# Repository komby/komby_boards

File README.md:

ftdi_prog
=========

Eagle files for the komby FTDI programmers

for more information visit http://www.komby.com/ftdi_prog

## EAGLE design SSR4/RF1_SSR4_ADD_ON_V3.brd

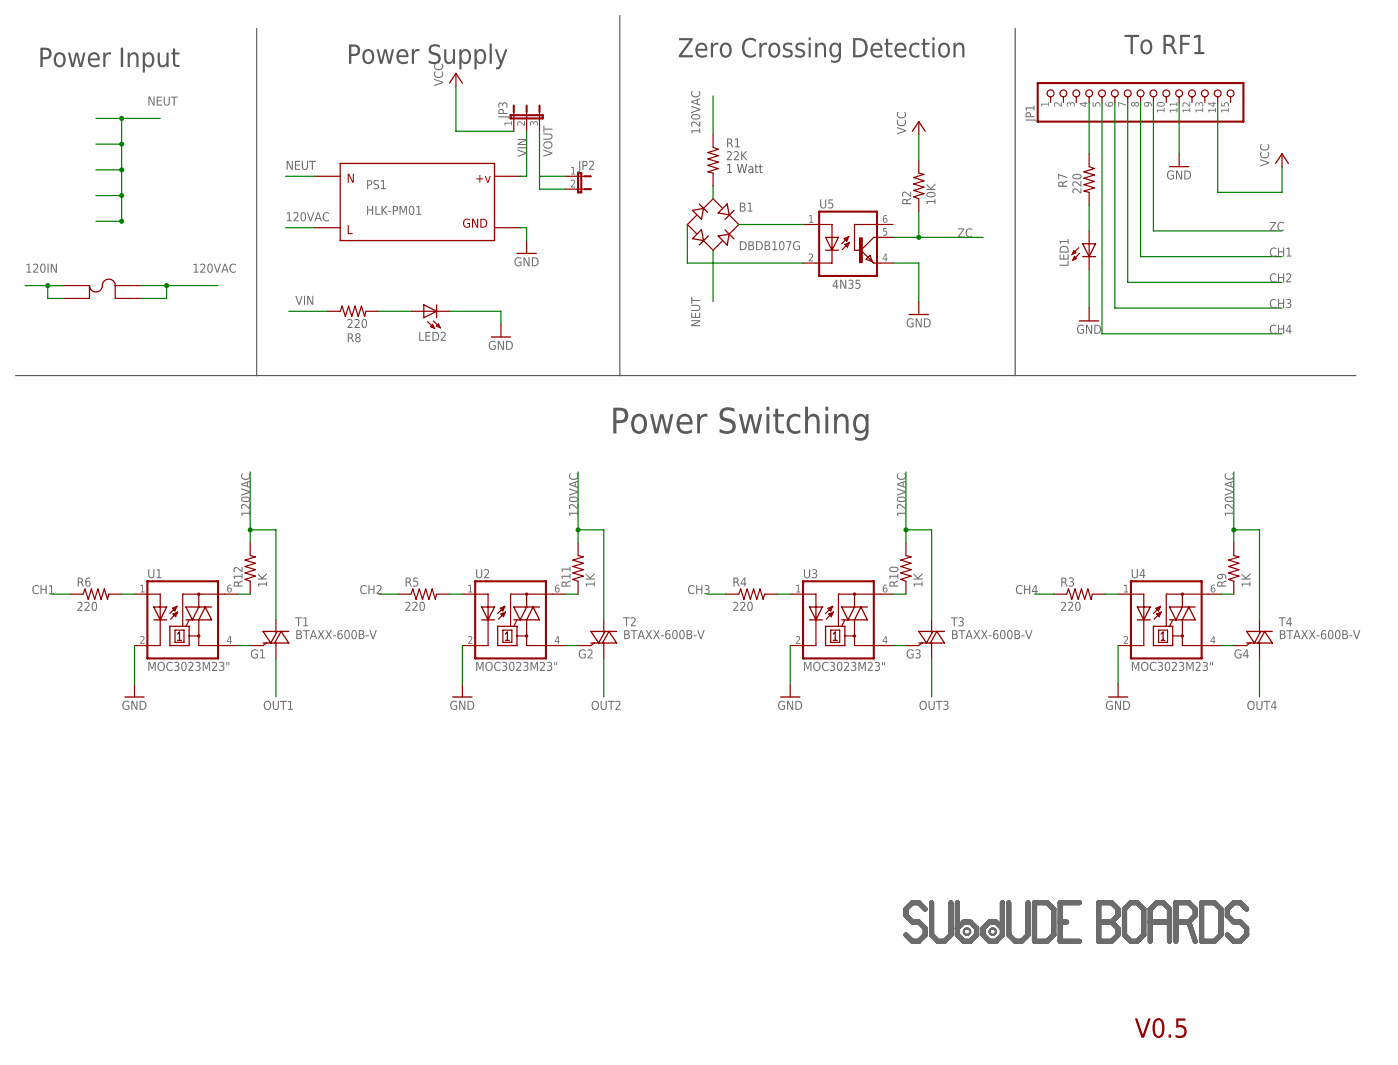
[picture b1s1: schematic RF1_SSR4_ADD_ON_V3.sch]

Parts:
B1: DBDB107G; DB
F1: FUSE5MMPCB; KE3517
JP1: PINHD-1X15; 1X15
JP2: JP1E; JP1
JP3: JP2E; JP2
LED1, LED2: LED3MM
PS1: HLK-PM01; HLK-PM01-STD
R1: 22K; 0617V
R2: 10K; 0207/7
R3, R4, R5, R6, R7, R8: 220; 0207/2V
R9, R10, R11, R12: 1K; 0207/2V
T1, T2, T3, T4: BTAXX-600B-V; TO220BV
U1, U2, U3, U4: MOC3023M23"; DIL06A
U5: 4N35SMALL; DIL06A
U$1, U$2: SUBDUDE_LOGOLARGE; SUBDUDE_LARGE

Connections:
120IN: F1.P$1, F1.P$3
120VAC: F1.P$2, F1.P$4, PS1.AC_L, R1.1, R9.2, R10.2, R11.2, R12.2, T1.T2 (A2), T2.T2 (A2), T3.T2 (A2), T4.T2 (A2)
CH1: JP1.8, R6.1
CH2: JP1.7, R5.1
CH3: JP1.6, R4.1
CH4: JP1.5, R3.1
G1: T1.G, U1.4 (A1)
G2: T2.G, U2.4 (A1)
G3: T3.G, U3.4 (A1)
G4: T4.G, U4.4 (A1)
GND: JP1.11, LED1.K (C), LED2.K (C), PS1.VO-, U1.2 (C), U2.2 (C), U3.2 (C), U4.2 (C), U5.4 (EMI)
unnamed: LED1.A, R7.2
unnamed: B1.AC1, R1.2
unnamed: JP1.4, R7.1
unnamed: LED2.A, R8.2
unnamed: B1.+, U5.1 (A)
unnamed: B1.-, U5.2 (C)
unnamed: R4.2, U3.1 (A)
unnamed: R5.2, U2.1 (A)
unnamed: R6.2, U1.1 (A)
unnamed: R9.1, U4.6 (A2)
unnamed: R10.1, U3.6 (A2)
unnamed: R11.1, U2.6 (A2)
unnamed: R12.1, U1.6 (A2)
NEUT: B1.AC2, PS1.AC_N
OUT1: T1.T1 (A1)
OUT2: T2.T1 (A1)
OUT3: T3.T1 (A1)
OUT4: T4.T1 (A1)
QQQQ: R3.2, U4.1 (A)
VCC: JP1.14, JP3.1, R2.2
VIN: JP3.2, PS1.VO+, R8.1
VOUT: JP2.1, JP2.2, JP3.3
ZC: JP1.9, R2.1, U5.5 (COL)

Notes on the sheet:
V0.5
Zero Crossing Detection
1 Watt
4N35
Power Supply
Power Input
To RF1
Power Switching

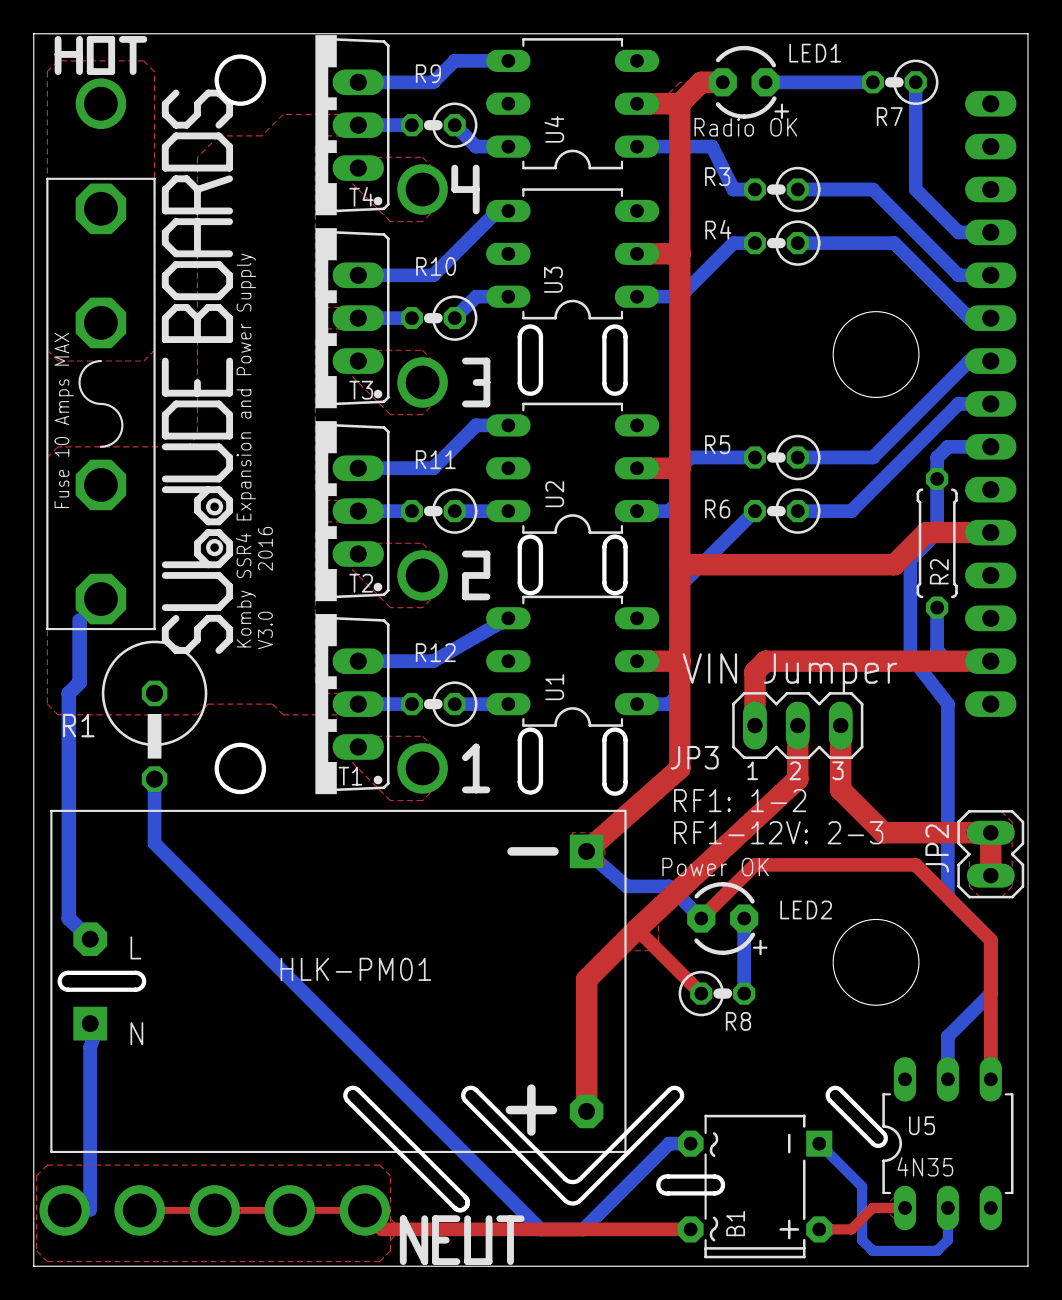
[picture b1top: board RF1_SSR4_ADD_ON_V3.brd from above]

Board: 2 copper layers, 58.9 x 73.0 mm, 31 parts (1 on the bottom side), 30 nets.

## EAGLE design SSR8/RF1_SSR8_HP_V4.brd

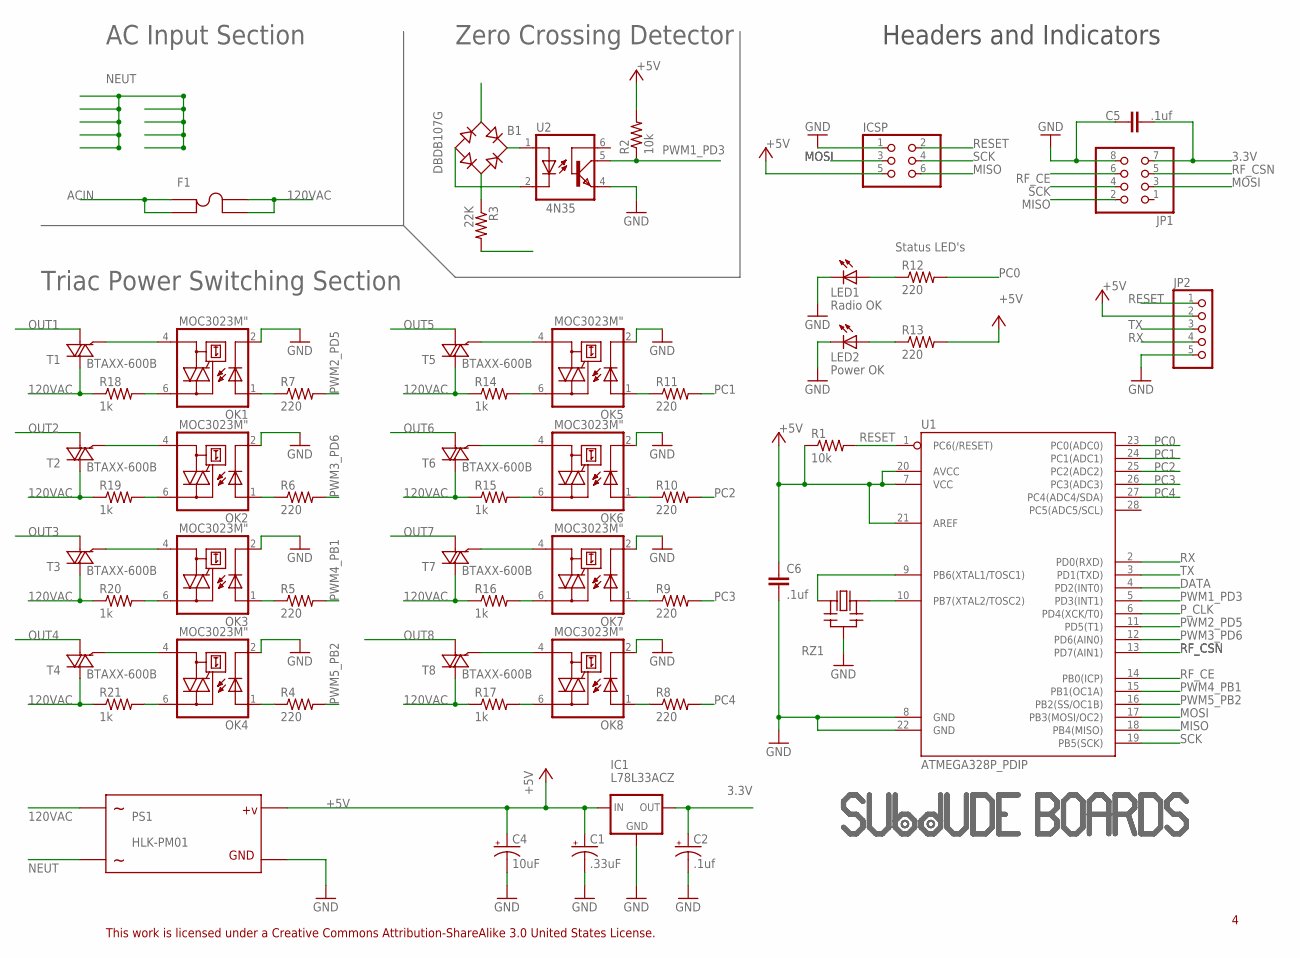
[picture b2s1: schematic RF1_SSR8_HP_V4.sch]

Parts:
B1: DBDB107G; DB
C1: .33uF; E1,8-4
C2: .1uf; E1,8-4
C4: 10uF; E1,8-4
C5, C6: .1uf; C025-024X044
F1: FUSE5MMPCB; KE3517
IC1: L78L33ACZ; 78LXX
ICSP: PINHD-2X3; 2X03
JP1: PINHD-2X4; 2X04
JP2: PINHD-1X51X05-BIG; 1X05-BIG
LED1, LED2: LED3MM
OK1, OK2, OK3, OK4, OK5, OK6, OK7, OK8: MOC3023M"; DIL06A
PS1: HLK-PM01; HLK-PM01-STD
R1: 10k; 0207/7
R2: 10k; 0207/2V
R3: 22K; 0411/12
R4, R5, R6, R7, R8, R9, R10, R11, R12, R13: 220; 0207/2V
R14, R15, R16, R17, R18, R19, R20, R21: 1k; 0207/2V
RZ1: CERMOSCILL-THM; CERM_OSC
T1, T2, T3, T4, T5, T6, T7, T8: BTAXX-600B; TO220BVA
U1: ATMEGA328P_PDIP; DIL28-3
U2: 4N35SMALL; DIL06A
U$2: SUBDUDE_LOGOLARGE; SUBDUDE_LARGE
U$3: SUBDUDE_LOGOSMALL; SUBDUDE_SMALL

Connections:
3.3V: C2.+, C5.2, IC1.OUT, JP1.7
120VAC: F1.P$2, F1.P$4, PS1.AC_N, R3.2, R14.1, R15.1, R16.1, R17.1, R18.1, R19.1, R20.1, R21.1, T1.T2 (A2), T2.T2 (A2), T3.T2 (A2), T4.T2 (A2), T5.T2 (A2), T6.T2 (A2), T7.T2 (A2), T8.T2 (A2)
+5V: C1.+, C4.+, C6.1, IC1.IN, ICSP.5, JP2.2, PS1.VO+, R1.1, R2.2, R13.2, U1.7 (VCC), U1.20 (AVCC), U1.21 (AREF)
ACIN: F1.P$1, F1.P$3
DATA: U1.4 (PD2(INT0))
GND: C1.-, C2.-, C4.-, C5.1, C6.2, IC1.GND, ICSP.1, JP1.8, JP2.5, LED1.K (C), LED2.K (C), OK1.2 (C), OK2.2 (C), OK3.2 (C), OK4.2 (C), OK5.2 (C), OK6.2 (C), OK7.2 (C), OK8.2 (C), PS1.VO-, RZ1.P$2 (GND), U1.8 (GND), U1.22 (GND), U2.4 (EMI)
MISO: ICSP.6, JP1.2, U1.18 (PB4(MISO))
MOSI: ICSP.3, JP1.3, U1.17 (PB3(MOSI/OC2))
unnamed: OK1.1 (A), R7.1
unnamed: OK2.1 (A), R6.1
unnamed: OK3.1 (A), R5.1
unnamed: OK4.1 (A), R4.1
unnamed: RZ1.P$3 (OUT), U1.10 (PB7(XTAL2/TOSC2))
unnamed: RZ1.P$1 (IN), U1.9 (PB6(XTAL1/TOSC1))
unnamed: OK5.1 (A), R11.1
unnamed: OK6.1 (A), R10.1
unnamed: OK7.1 (A), R9.1
unnamed: OK8.1 (A), R8.1
unnamed: B1.AC2, R3.1
unnamed: OK1.6 (A2), R18.2
unnamed: OK1.4 (A1), T1.G
unnamed: OK2.6 (A2), R19.2
unnamed: OK2.4 (A1), T2.G
unnamed: OK3.6 (A2), R20.2
unnamed: OK3.4 (A1), T3.G
unnamed: OK4.6 (A2), R21.2
unnamed: B1.-, U2.2 (C)
unnamed: B1.+, U2.1 (A)
unnamed: OK4.4 (A1), T4.G
unnamed: LED1.A, R12.1
unnamed: LED2.A, R13.1
unnamed: OK5.4 (A1), T5.G
unnamed: OK5.6 (A2), R14.2
unnamed: OK6.4 (A1), T6.G
unnamed: OK6.6 (A2), R15.2
unnamed: OK7.4 (A1), T7.G
unnamed: OK7.6 (A2), R16.2
unnamed: OK8.6 (A2), R17.2
unnamed: OK8.4 (A1), T8.G
NEUT: B1.AC1, PS1.AC_L
OUT1: T1.T1 (A1)
OUT2: T2.T1 (A1)
OUT3: T3.T1 (A1)
OUT4: T4.T1 (A1)
OUT5: T5.T1 (A1)
OUT6: T6.T1 (A1)
OUT7: T7.T1 (A1)
OUT8: T8.T1 (A1)
PC0: R12.2, U1.23 (PC0(ADC0))
PC1: R11.2, U1.24 (PC1(ADC1))
PC2: R10.2, U1.25 (PC2(ADC2))
PC3: R9.2, U1.26 (PC3(ADC3))
PC4: R8.2, U1.27 (PC4(ADC4/SDA))
PWM1_PD3: R2.1, U1.5 (PD3(INT1)), U2.5 (COL)
PWM2_PD5: R7.2, U1.11 (PD5(T1))
PWM3_PD6: R6.2, U1.12 (PD6(AIN0))
PWM4_PB1: R5.2, U1.15 (PB1(OC1A))
PWM5_PB2: R4.2, U1.16 (PB2(SS/OC1B))
P_CLK: U1.6 (PD4(XCK/T0))
RESET: ICSP.2, JP2.1, R1.2, U1.1 (PC6(/RESET))
RF_CE: JP1.6, U1.14 (PB0(ICP))
RF_CSN: JP1.5, U1.13 (PD7(AIN1))
RX: JP2.4, U1.2 (PD0(RXD))
SCK: ICSP.4, JP1.4, U1.19 (PB5(SCK))
TX: JP2.3, U1.3 (PD1(TXD))

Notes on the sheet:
This work is licensed under a Creative Commons Attribution-ShareAlike 3.0 United States License.
AC Input Section
Status LED's
Zero Crossing Detector
Triac Power Switching Section
Power OK
Radio OK
Headers and Indicators
4N35

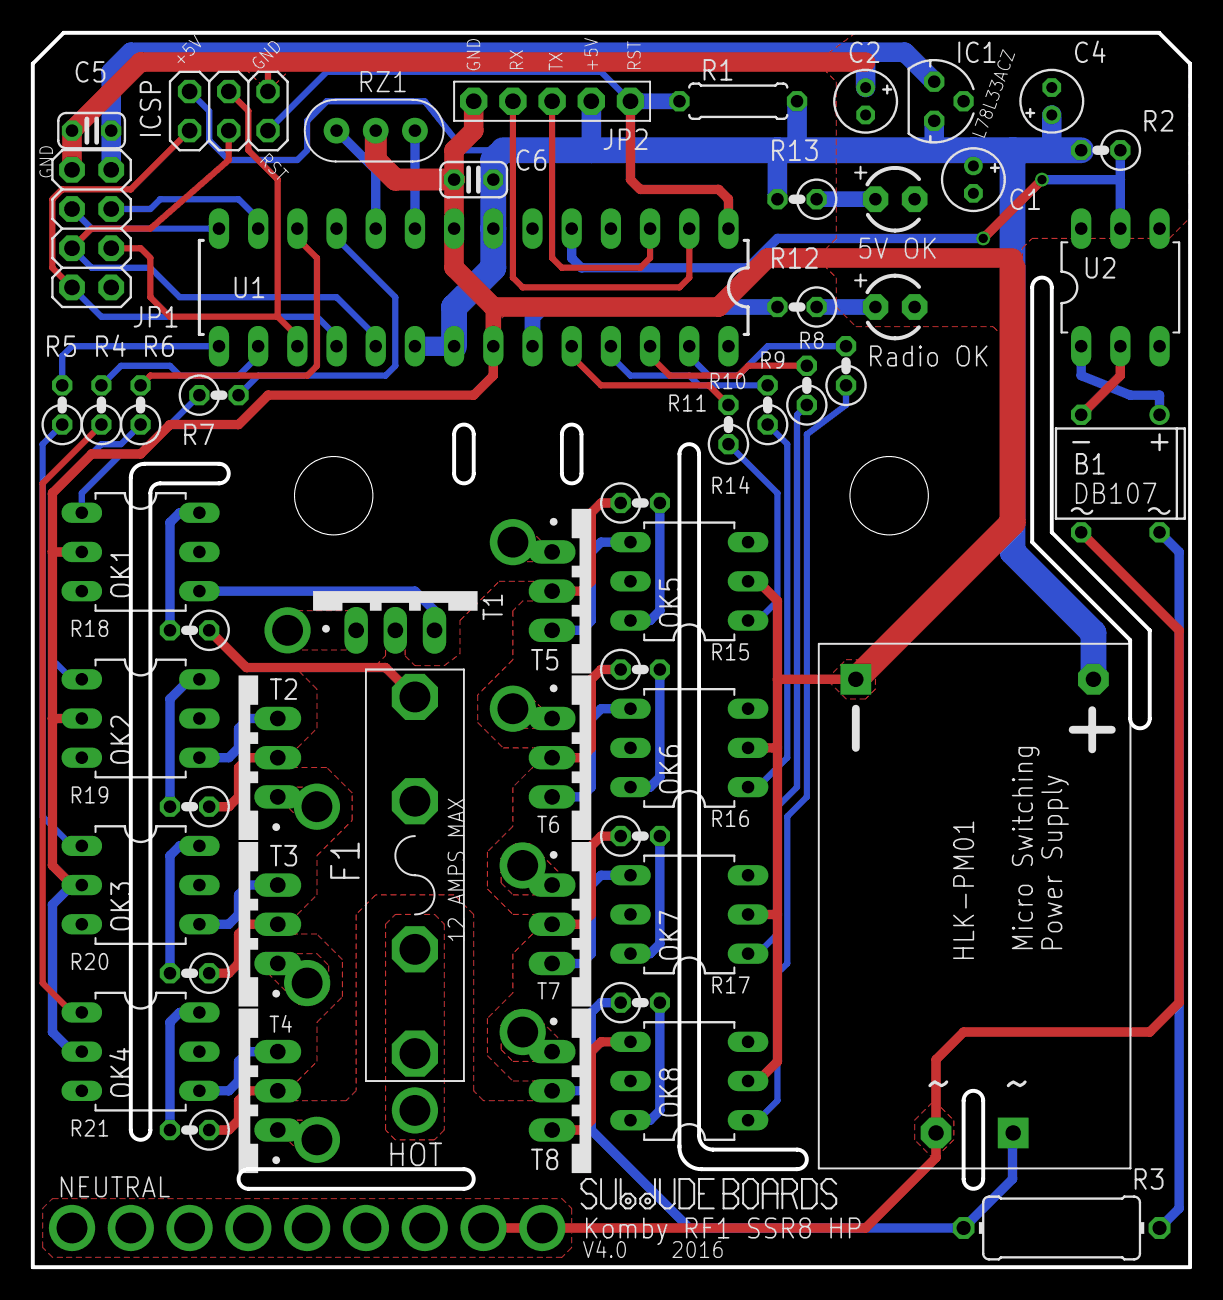
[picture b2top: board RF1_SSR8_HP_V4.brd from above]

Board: 2 copper layers, 75.0 x 80.0 mm, 56 parts (1 on the bottom side), 55 nets.

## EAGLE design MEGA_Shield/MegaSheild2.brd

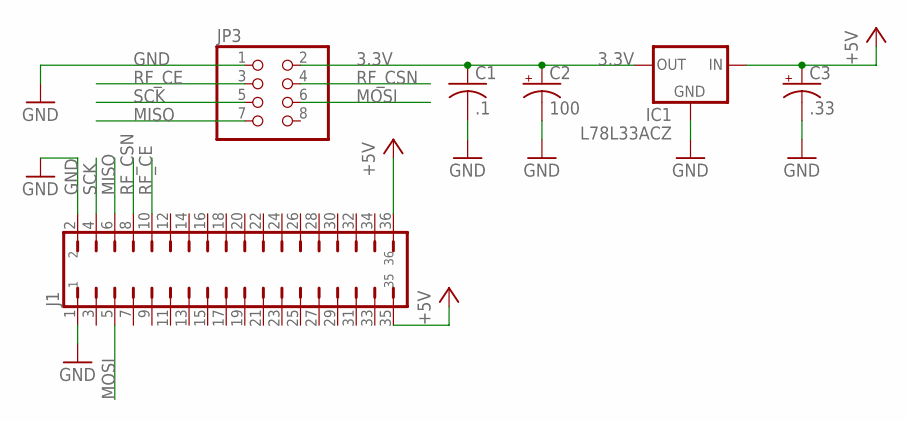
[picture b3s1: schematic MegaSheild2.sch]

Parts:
C1: .1; C025-024X044
C2: 100; E2,5-6
C3: .33; E1,8-4
IC1: L78L33ACZ; 78LXX
J1: JP18Q2X18BIG; 2X18-BIG
JP3: PINHD-2X4; 2X04

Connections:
3.3V: C1.1, C2.+, IC1.OUT, JP3.2
+5V: C3.+, IC1.IN, J1.35, J1.36
GND: C1.2, C2.-, C3.-, IC1.GND, J1.1, J1.2, JP3.1
MISO: J1.6, JP3.7
MOSI: J1.5, JP3.6
RF_CE: J1.10, JP3.3
RF_CSN: J1.8, JP3.4
SCK: J1.4, JP3.5

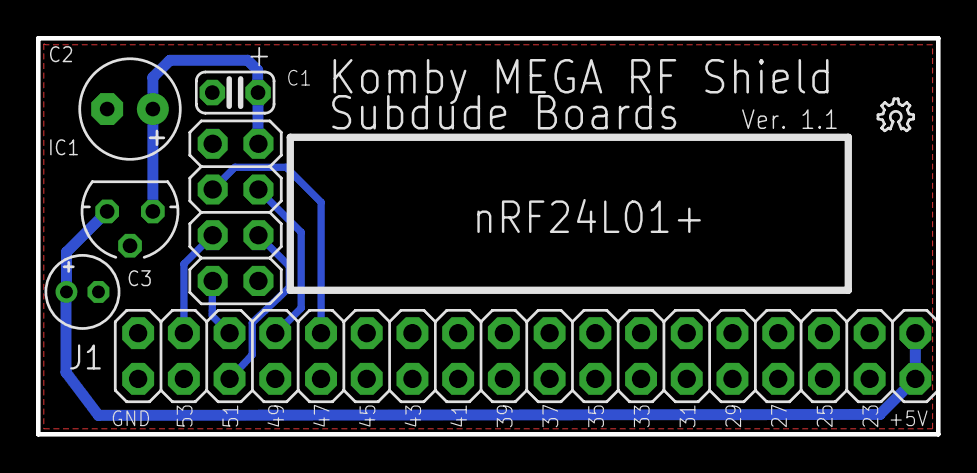
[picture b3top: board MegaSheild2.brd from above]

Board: 2 copper layers, 50.0 x 22.0 mm, 7 parts (0 on the bottom side), 8 nets.

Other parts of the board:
U$1: OSHW_6X70_NOTEXT

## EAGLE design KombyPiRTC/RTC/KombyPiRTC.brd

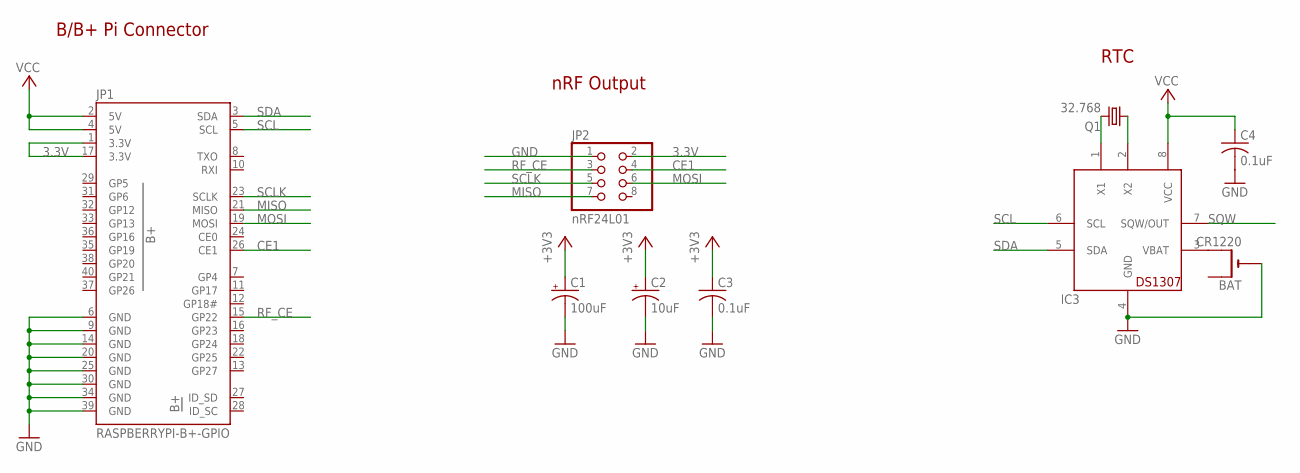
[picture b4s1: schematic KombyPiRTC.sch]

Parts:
BAT: CR1220; CR1220-THM
C1: 100uF; CPOL-RADIAL-100UF-25V
C2: 10uF; CPOL-RADIAL-10UF-25V
C3, C4: 0.1uF; C025-025X050
IC3: DS1307; DIL08
JP1: RASPBERRYPI-B+-GPIO; 2X20-SHROUDED
JP2: nRF24L01; 2X04
Q1: 32.768; TC38H

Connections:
3.3V: C1.1 (+), C2.1 (+), C3.1, JP1.1 (3.3V), JP1.17 (3.3V), JP2.2 (VCC)
CE1: JP1.26 (CE1), JP2.4 (CSN)
GND: BAT.-, C1.2 (-), C2.2 (-), C3.2, C4.2, IC3.4 (GND), JP1.6 (GND), JP1.9 (GND), JP1.14 (GND), JP1.20 (GND), JP1.25 (GND), JP1.30 (GND), JP1.34 (GND), JP1.39 (GND), JP2.1 (GND)
MISO: JP1.21 (MISO), JP2.7 (MISO)
MOSI: JP1.19 (MOSI), JP2.6 (MOSI)
unnamed: IC3.1 (X1), Q1.2
unnamed: IC3.2 (X2), Q1.1
unnamed: BAT.+2 (+1), IC3.3 (VBAT)
RF_CE: JP1.15 (GP22), JP2.3 (CE)
SCL: IC3.6 (SCL), JP1.5 (SCL)
SCLK: JP1.23 (SCLK), JP2.5 (SCK)
SDA: IC3.5 (SDA), JP1.3 (SDA)
SQW: IC3.7 (SQW/OUT)
VCC: C4.1, IC3.8 (VCC), JP1.2 (5V), JP1.4 (5V)

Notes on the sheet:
nRF Output
B/B+ Pi Connector
RTC

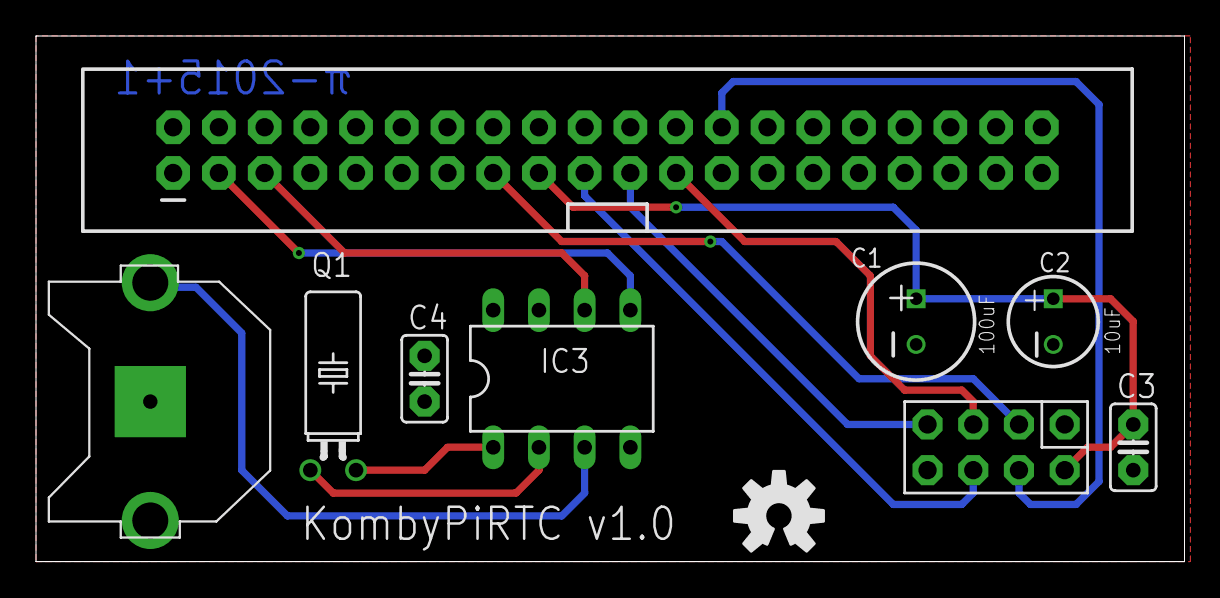
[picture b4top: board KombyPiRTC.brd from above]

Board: 2 copper layers, 63.8 x 29.2 mm, 10 parts (0 on the bottom side), 13 nets.

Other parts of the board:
U$3: OSHW-LOGO-M

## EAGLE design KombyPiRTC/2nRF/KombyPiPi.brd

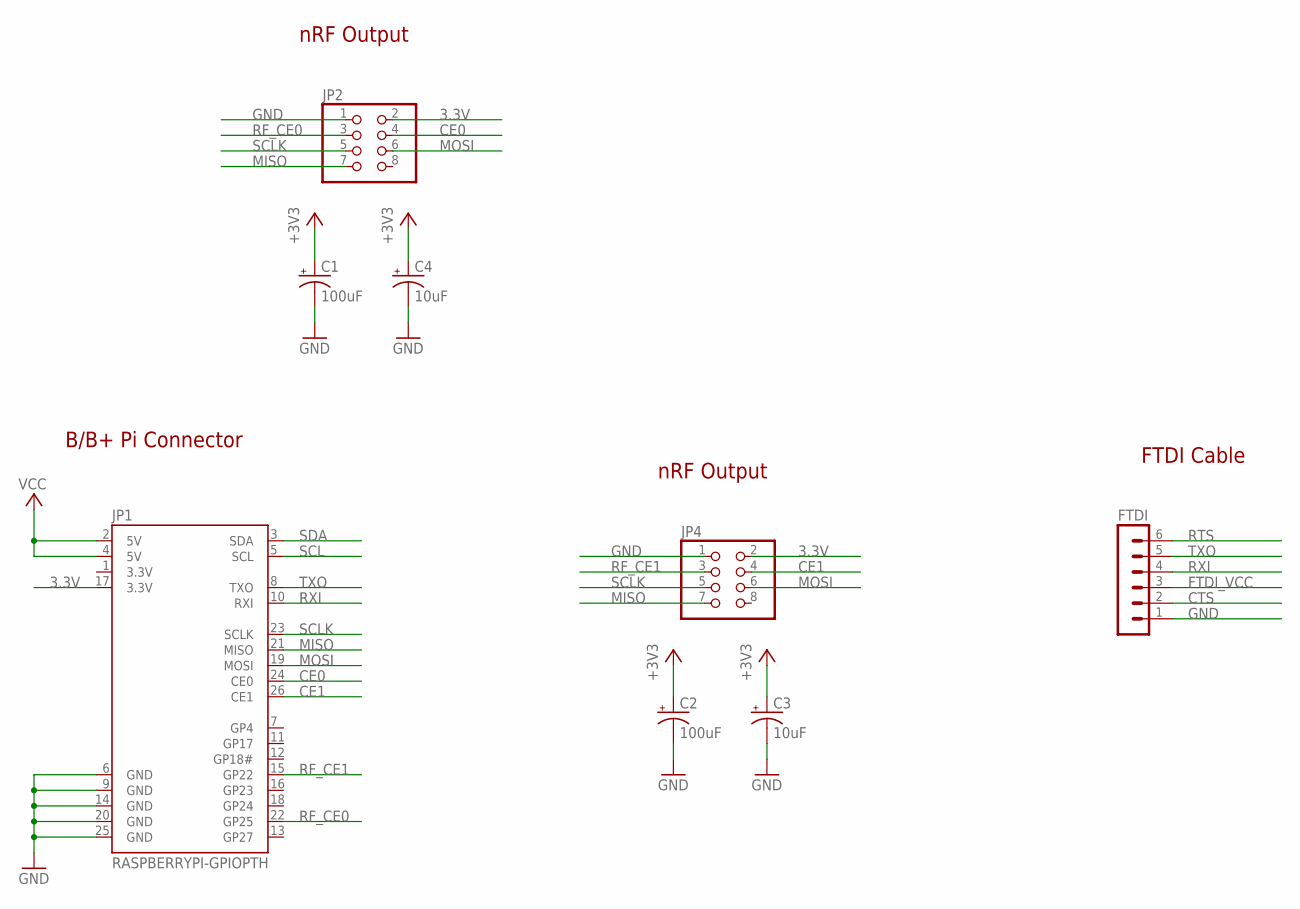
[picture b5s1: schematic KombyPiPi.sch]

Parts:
C1, C2: 100uF; CPOL-RADIAL-100UF-25V
C3, C4: 10uF; CPOL-RADIAL-10UF-25V
FTDI: MA06-1
JP1: RASPBERRYPI-GPIOPTH; 2X13-SHROUDED
JP2, JP4: PINHD-2X4; 2X04

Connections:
3.3V: C1.1 (+), C2.1 (+), C3.1 (+), C4.1 (+), JP1.1 (3.3V), JP1.17 (3.3V), JP2.2, JP4.2
CE0: JP1.24 (CE0), JP2.4
CE1: JP1.26 (CE1), JP4.4
CTS: FTDI.2
FTDI_VCC: FTDI.3
GND: C1.2 (-), C2.2 (-), C3.2 (-), C4.2 (-), FTDI.1, JP1.6 (GND), JP1.9 (GND), JP1.14 (GND), JP1.20 (GND), JP1.25 (GND), JP2.1, JP4.1
MISO: JP1.21 (MISO), JP2.7, JP4.7
MOSI: JP1.19 (MOSI), JP2.6, JP4.6
RF_CE0: JP1.22 (GP25), JP2.3
RF_CE1: JP1.15 (GP22), JP4.3
RTS: FTDI.6
RXI: FTDI.4, JP1.10 (RXI)
SCL: JP1.5 (SCL)
SCLK: JP1.23 (SCLK), JP2.5, JP4.5
SDA: JP1.3 (SDA)
TXO: FTDI.5, JP1.8 (TXO)
VCC: JP1.2 (5V), JP1.4 (5V)

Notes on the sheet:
nRF Output
B/B+ Pi Connector
FTDI Cable

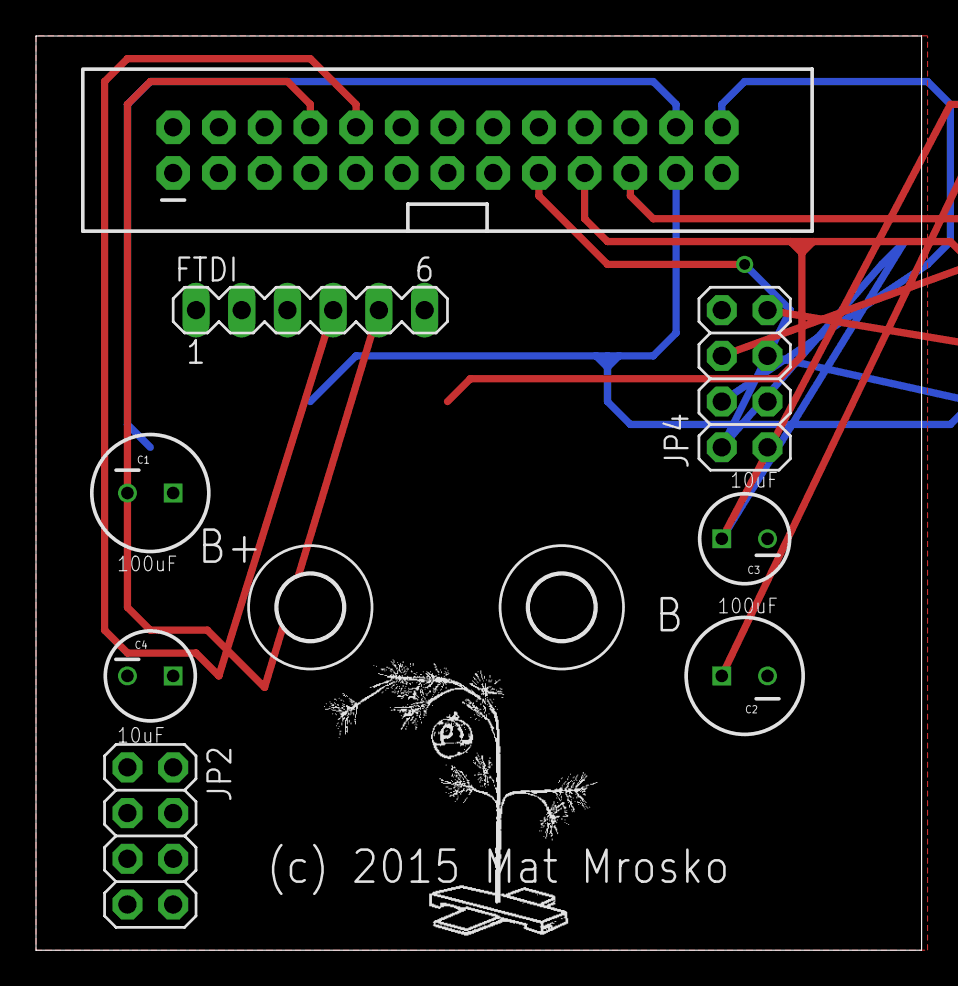
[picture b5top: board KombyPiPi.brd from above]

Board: 2 copper layers, 49.2 x 50.8 mm, 11 parts (0 on the bottom side), 12 nets.

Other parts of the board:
U$1, U$2: 3,6
U$3: DIYC

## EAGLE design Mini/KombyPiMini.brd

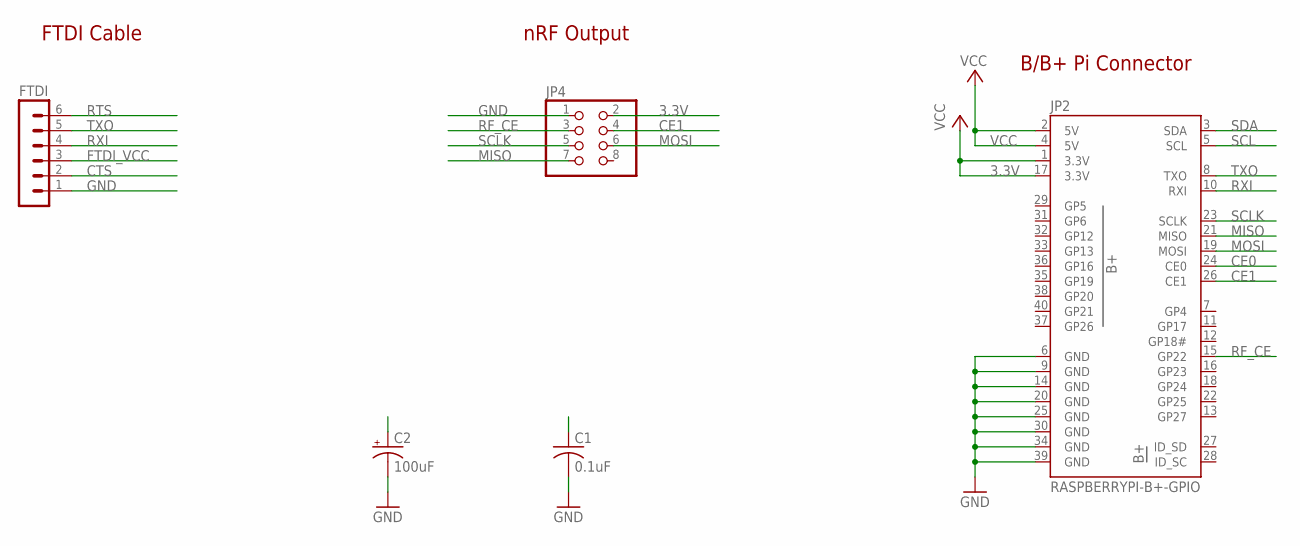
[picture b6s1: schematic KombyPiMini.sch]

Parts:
C1: 0.1uF; C025-025X050
C2: 100uF; E5-6
FTDI: MA06-1
JP2: RASPBERRYPI-B+-GPIO; 2X20-SHROUDED
JP4: PINHD-2X4; 2X04

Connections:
3.3V: C1.1, C2.+, JP2.1 (3.3V), JP2.17 (3.3V), JP4.2
CE0: JP2.24 (CE0)
CE1: JP2.26 (CE1), JP4.4
CTS: FTDI.2
FTDI_VCC: FTDI.3
GND: C1.2, C2.-, FTDI.1, JP2.6 (GND), JP2.9 (GND), JP2.14 (GND), JP2.20 (GND), JP2.25 (GND), JP2.30 (GND), JP2.34 (GND), JP2.39 (GND), JP4.1
MISO: JP2.21 (MISO), JP4.7
MOSI: JP2.19 (MOSI), JP4.6
RF_CE: JP2.15 (GP22), JP4.3
RTS: FTDI.6
RXI: FTDI.4, JP2.10 (RXI)
SCL: JP2.5 (SCL)
SCLK: JP2.23 (SCLK), JP4.5
SDA: JP2.3 (SDA)
TXO: FTDI.5, JP2.8 (TXO)
VCC: JP2.2 (5V), JP2.4 (5V)

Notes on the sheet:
nRF Output
B/B+ Pi Connector
FTDI Cable

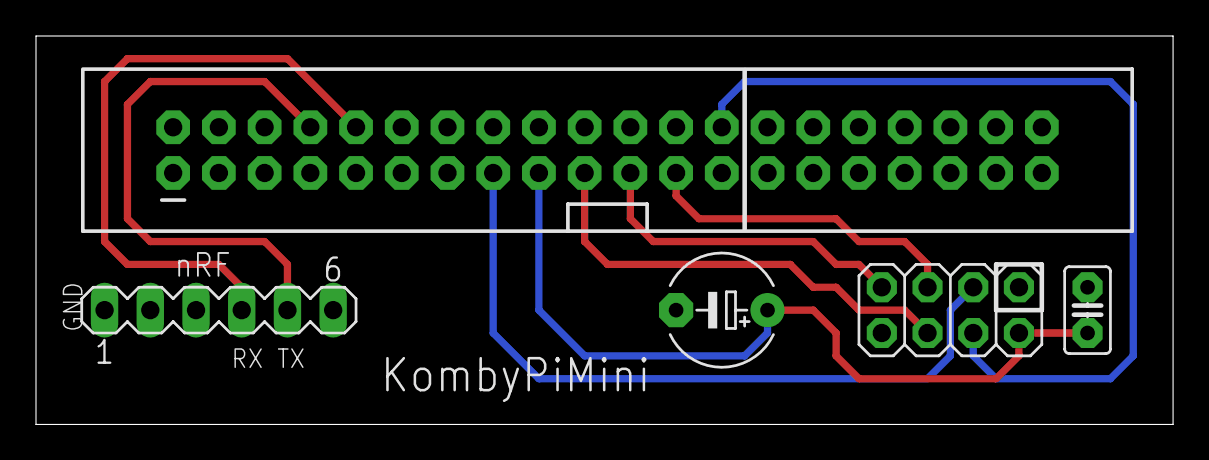
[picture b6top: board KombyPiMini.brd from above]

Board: 2 copper layers, 63.2 x 21.6 mm, 5 parts (0 on the bottom side), 10 nets.

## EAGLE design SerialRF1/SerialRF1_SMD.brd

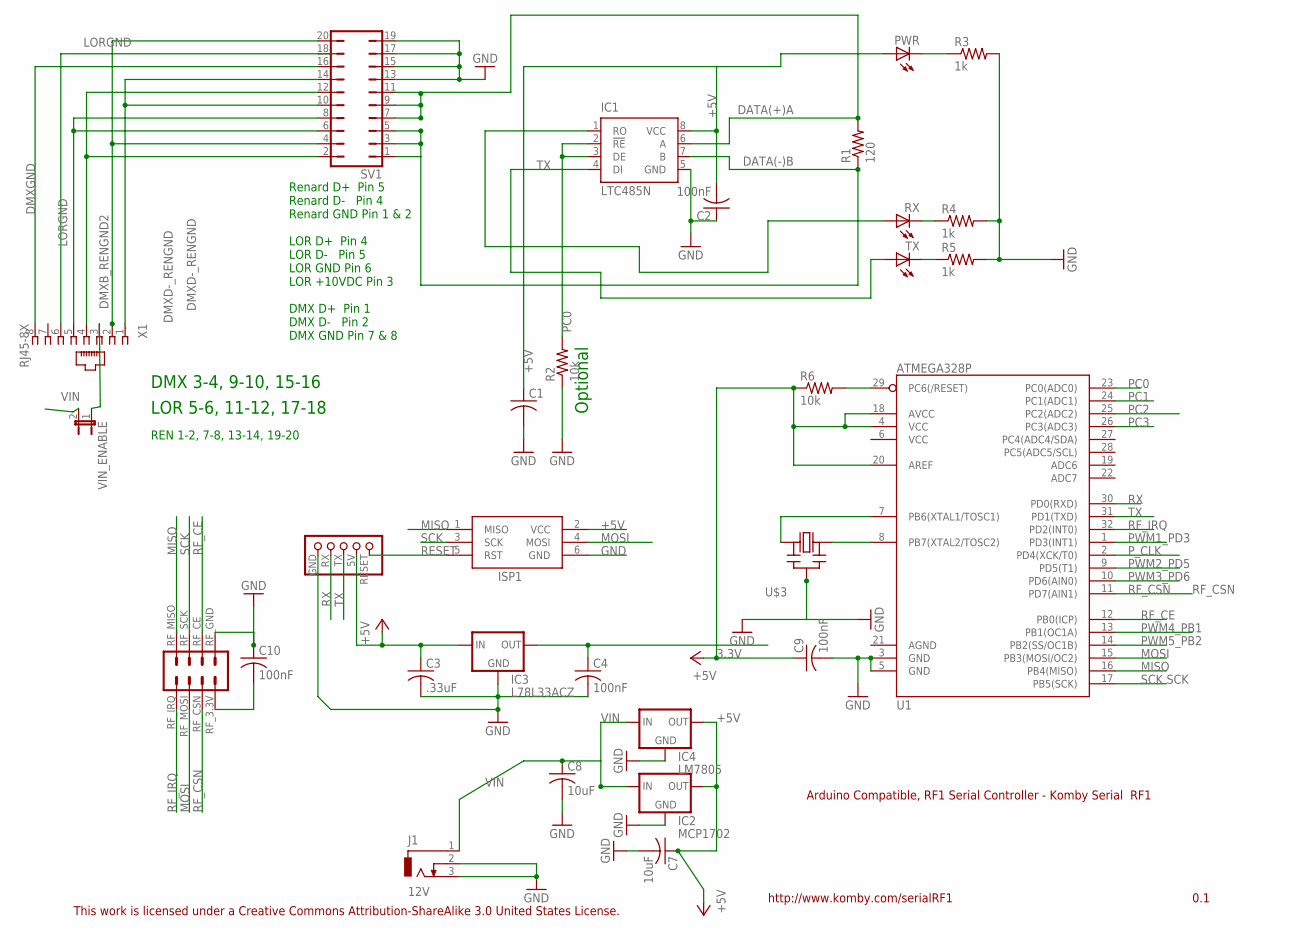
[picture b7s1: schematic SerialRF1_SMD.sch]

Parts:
C1: C-USC0805K; C0805K
C2, C4, C9, C10: 100nF; C0805K
C3: .33uF; C0805K
C7, C8: 10uF; C0805K
IC1: LTC485N; DIL08
IC2: MCP1702; TO92
IC3: L78L33ACZ; 78LXX
IC4: LM7805; TO220-IGO
ISP1: AVRISP-6; AVRISP
J1: 12V; DCJ0303
PWR: LEDSML0805; SML0805
R1: 120; R0805W
R2: 10k; R0805W
R3, R4, R5: 1k; M0805
R6: 10k; R0805
RX: LEDSML0805; SML0805
SV1: JP10Q
TX: LEDSML0805; SML0805
U1: ATMEGA328P; TQFP32-08
U$3: CERMOSCILL-THM; CERM_OSC
U$4: KOMBY_TTL_SERIAL; KOMBY_SERIAL_FOOTPRINT
U$6: NRF24L01_HEADER; NRF24L01
VIN_ENABLE: JP1E; JP1
X1: RJ45-8X; RJ45-NO-SHIELD

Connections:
3.3V: C4.1, IC3.OUT
+5V: C1.1, C2.2, C3.1, C7.1, C9.1, IC1.8 (VCC), IC2.3 (OUT), IC3.IN, IC4.OUT, ISP1.2 (VCC), PWR.A, R6.1, U1.4 (VCC), U1.18 (AVCC), U1.20 (AREF), U$4.5V
DATA(+)A: IC1.6 (A), R1.2, SV1.7, SV1.9, SV1.11
DATA(-)B: IC1.7 (B), R1.1, SV1.1, SV1.3, SV1.5
DMXB_RENGND2: SV1.4, SV1.20, X1.2
DMXD-_RENGND: SV1.10, SV1.14, X1.1
DMXGND: SV1.16, X1.8
GND: C1.2, C2.1, C3.2, C4.2, C7.2, C8.2, C9.2, C10.1, IC1.5 (GND), IC2.1 (GND), IC3.GND, IC4.GND, ISP1.6 (GND), J1.2, J1.3, R2.1, R3.2, R4.2, R5.2, SV1.13, SV1.15, SV1.17, SV1.19, U1.3 (GND), U1.5 (GND), U$3.P$2 (GND), U$4.GND, U$6.RF_GND (RFGND_1)
LORGND: SV1.18, X1.6
MISO: ISP1.1 (MISO), U1.16 (PB4(MISO)), U$6.RF_MISO
MOSI: ISP1.4 (MOSI), U1.15 (PB3(MOSI/OC2)), U$6.RF_MOSI
unnamed: SV1.6, SV1.8, X1.5
unnamed: SV1.2, SV1.12, X1.4
unnamed: VIN_ENABLE.1, X1.3
unnamed: PWR.C, R3.1
unnamed: R4.1, RX.C
unnamed: R5.1, TX.C
unnamed: U1.8 (PB7(XTAL2/TOSC2)), U$3.P$3 (OUT)
unnamed: U1.7 (PB6(XTAL1/TOSC1)), U$3.P$1 (IN)
unnamed: C10.2, U$6.RF_3.3V
PC0: IC1.2 (!RE), IC1.3 (DE), R2.2, U1.23 (PC0(ADC0))
PC1: U1.24 (PC1(ADC1))
PC2: U1.25 (PC2(ADC2))
PC3: U1.26 (PC3(ADC3))
PWM1_PD3: U1.1 (PD3(INT1))
PWM2_PD5: U1.9 (PD5(T1))
PWM3_PD6: U1.10 (PD6(AIN0))
PWM4_PB1: U1.13 (PB1(OC1A))
PWM5_PB2: U1.14 (PB2(SS/OC1B))
P_CLK: U1.2 (PD4(XCK/T0))
RESET: ISP1.5 (RST), R6.2, U1.29 (PC6(/RESET)), U$4.RESET
RF_CE: U1.12 (PB0(ICP)), U$6.RF_CE
RF_CSN: U1.11 (PD7(AIN1)), U$6.RF_CSN
RF_IRQ: U1.32 (PD2(INT0)), U$6.RF_IRQ
RX: IC1.1 (RO), RX.A, U1.30 (PD0(RXD)), U$4.RX
SCK: ISP1.3 (SCK), U1.17 (PB5(SCK)), U$6.RF_SCK
TX: IC1.4 (DI), TX.A, U1.31 (PD1(TXD)), U$4.TX
VIN: C8.1, IC2.2 (IN), IC4.IN, J1.1, VIN_ENABLE.2

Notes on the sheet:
Arduino Compatible, RF1 Serial Controller - Komby Serial RF1
0.1
http://www.komby.com/serialRF1
This work is licensed under a Creative Commons Attribution-ShareAlike 3.0 United States License.
DMX 3-4, 9-10, 15-16
LOR 5-6, 11-12, 17-18
REN 1-2, 7-8, 13-14, 19-20
Optional
Renard D+ Pin 5 Renard D- Pin 4 Renard GND Pin 1 & 2 LOR D+ Pin 4 LOR D- Pin 5 LOR GND Pin 6 LOR +10VDC Pin 3 DMX D+ Pin 1 DMX D- Pin 2 DMX GND Pin 7 & 8

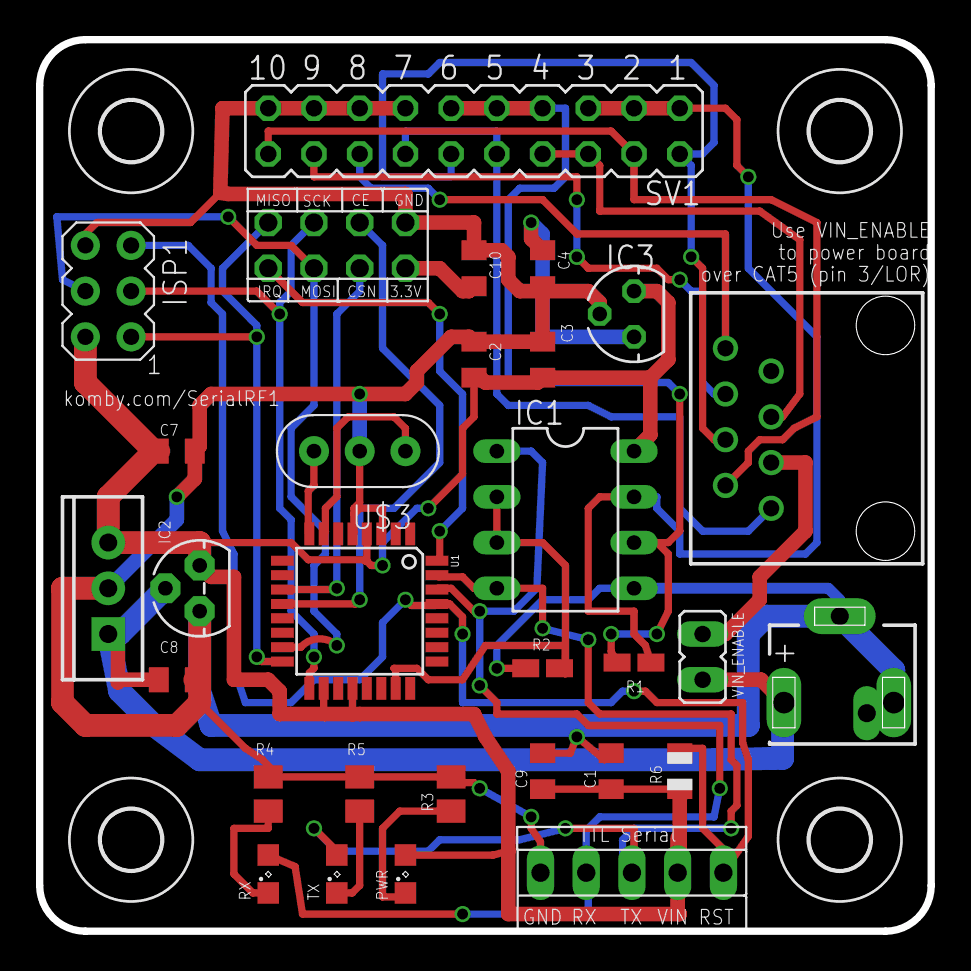
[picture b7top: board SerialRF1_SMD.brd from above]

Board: 2 copper layers, 49.5 x 49.5 mm, 34 parts (0 on the bottom side), 29 nets.

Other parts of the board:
U$1, U$2, U$7, U$8: 3,3

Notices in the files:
KombyPiRTC/2nRF/KombyPiPi.brd:
(c) 2015 Mat Mrosko
parts and their libraries:
SparkFun-Boards: Licensing: Creative Commons ShareAlike 4.0 International - https://creativecommons.org/licenses/by-sa/4.0
SparkFun-DigitalIC: Licensing: CC v3.0 Share-Alike You are welcome to use this library for commercial purposes.
